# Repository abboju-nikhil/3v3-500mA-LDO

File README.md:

# Single-Cell Li-Ion 3.3V / 500mA Low-Noise Power Supply

> A compact, robust, low-noise **3.3V linear regulator PCB** designed for **single-cell Li-ion batteries**, featuring comprehensive input protection, thermal optimization, and debugging support. Ideal for embedded systems, RF modules, sensors, and precision analog applications. 

---

## 📌 Overview

This project implements a **2-layer PCB** that converts the output of a **single-cell Li-ion battery (3.8V–4.2V)** into a clean, regulated **3.3V** supply capable of delivering up to **500mA** continuous current.

The design emphasizes:

* Low output noise
* High reliability
* Battery efficiency
* Robust input protection
* Thermal performance
* Easy testing and debugging

---

## ✨ Features

* 🔋 Single-cell Li-ion input (3.8V–4.2V)
* ⚡ Fixed 3.3V regulated output
* 🔌 500mA continuous output current
* 🛡 Reverse polarity protection
* ⚠ Resettable overcurrent protection (PTC Fuse)
* ⚡ TVS surge & ESD protection
* 🔥 Thermal pad with via array
* 💡 Power indication LED
* 📈 Dedicated test points
* 🧩 2-layer PCB with optimized power routing

---

## 📊 Specifications

| Parameter             | Value        |
| --------------------- | ------------ |
| Input Voltage         | 3.8V–4.2V DC |
| Output Voltage        | 3.3V DC      |
| Output Current        | 500mA Max    |
| Typical Load          | 450mA        |
| Operating Temperature | 0°C–70°C     |
| PCB Layers            | 2            |
| Board Size            | <40mm × 20mm |

---

# Architecture

```text
Li-Ion Battery
      │
      ▼
Resettable PTC Fuse
      │
      ▼
TVS Diode Protection
      │
      ▼
P-Channel MOSFET
(Reverse Polarity Protection)
      │
      ▼
LP5912-3.3 LDO
      │
      ▼
Output Capacitors
      │
      ▼
3.3V Output Connector
```

---

# Main Components

| Reference | Part           | Purpose                     |
| --------- | -------------- | --------------------------- |
| U1        | LP5912-3.3DRVR | 500mA Low-Noise LDO         |
| Q1        | DMP2035U-7     | Reverse Polarity Protection |
| F1        | MF-NSMF110-2   | Resettable PTC Fuse         |
| D1        | SMAJ5.0CA      | TVS Surge Protection        |
| D2        | BZT52C6V8      | MOSFET Gate Protection      |
| D3        | Green LED      | Power Indicator             |
| C1        | 22µF           | Input Bulk Capacitor        |
| C2        | 100nF          | Input Decoupling            |
| C3        | 10µF           | Output Stability            |
| C4        | 100nF          | High-Frequency Filtering    |

---

# Protection Features

## Reverse Polarity Protection

A **DMP2035U-7 P-Channel MOSFET** replaces the traditional Schottky diode, providing:

* Lower voltage drop
* Higher efficiency
* Better battery utilization
* Automatic reverse battery protection

---

## Overcurrent Protection

The **MF-NSMF110-2 resettable PTC fuse** protects against:

* Output short circuits
* Component failures
* Excessive current draw

The fuse automatically resets once the fault is removed.

---

## Surge & ESD Protection

A **SMAJ5.0CA TVS diode** protects the input from:

* ESD events
* Hot-plug transients
* Voltage spikes
* Input surges

---

## MOSFET Gate Protection

A **6.8V Zener diode (BZT52C6V8)** limits the gate-to-source voltage to protect the MOSFET during transient events.

---

# Capacitor Configuration

## Input Side

| Component | Function                       |
| --------- | ------------------------------ |
| 22µF      | Bulk energy storage            |
| 100nF     | High-frequency noise filtering |

Placed close to the regulator input to minimize parasitic inductance.

---

## Output Side

| Component | Function                       |
| --------- | ------------------------------ |
| 10µF      | Stability & transient response |
| 100nF     | High-frequency filtering       |

Located directly beside the regulator output pin.

---

# Test Points

For simplified debugging and validation:

| Test Point | Signal |
| ---------- | ------ |
| TP1        | VIN    |
| TP2        | VOUT   |
| TP3        | GND    |

Compatible with multimeters and oscilloscopes.

---

# Thermal Design

Worst-case power dissipation:

```text
P = (VIN − VOUT) × IOUT

= (4.2 − 3.3) × 0.5

≈ 0.45 W
```

Thermal improvements include:

* Exposed thermal pad
* Thermal via array
* Continuous ground plane
* Ground stitching vias

These features improve heat dissipation and ensure reliable operation within the specified temperature range.

---

# PCB Layout Highlights

* 2-layer PCB
* Continuous bottom ground plane
* Wide VIN/VOUT copper pours
* Short power paths
* Thermal vias beneath LDO
* Ground stitching
* 45° trace routing
* Clearly labeled silkscreen
* Dedicated debugging test points

---

# Applications

This board is suitable for:

* 🤖 Embedded Systems
* 📡 RF Modules
* 📟 IoT Devices
* 🌡 Sensor Nodes
* 🎧 Low-Noise Analog Circuits
* 🔬 Laboratory Prototypes
* 📷 Portable Electronics

---

# Repository Structure

```text
├── Hardware/
│   ├── Schematic/
│   ├── PCB/
│   ├── Gerbers/
│   └── BOM/
│
├── Images/
│   ├── PCB_3D.png
│   ├── Top_View.png
│   └── Bottom_View.png
│
├── Datasheets/
│
├── Docs/
│   └── Design_Notes.pdf
│
└── README.md
```

---

# Future Improvements

* Buck-Boost version for full battery discharge operation
* Battery charging circuit integration
* Fuel gauge implementation
* USB Type-C power input
* Power-path management
* Load switch enable/disable control

---

# License

This project is released under the **MIT License**.

---

## 👨‍💻 Author

**Nikhil Abboju**
Power Electronics Engineer | PCB Design | Embedded Hardware | KiCad

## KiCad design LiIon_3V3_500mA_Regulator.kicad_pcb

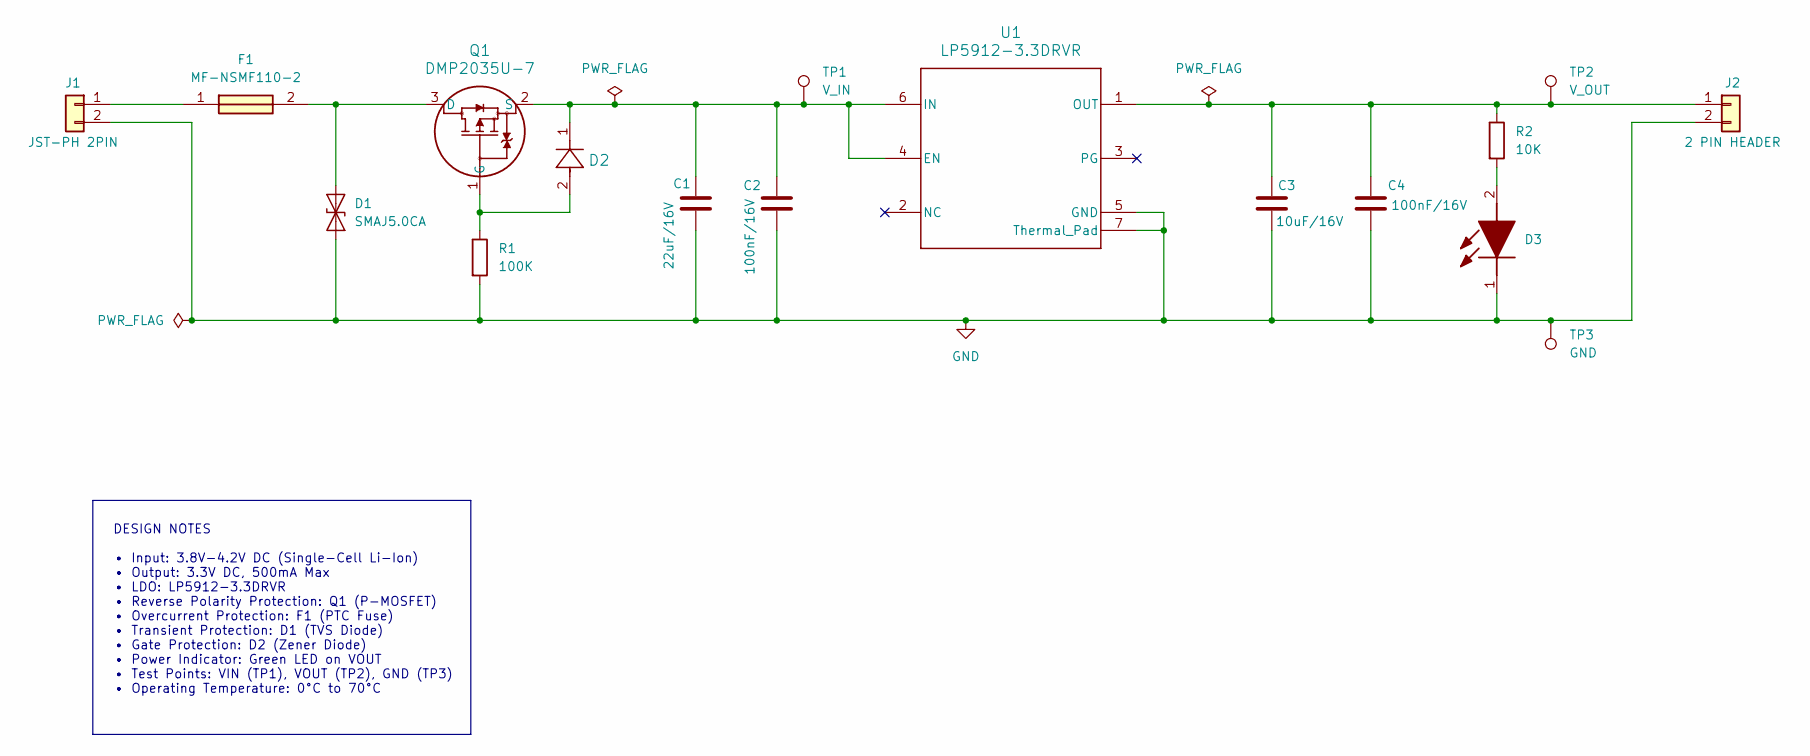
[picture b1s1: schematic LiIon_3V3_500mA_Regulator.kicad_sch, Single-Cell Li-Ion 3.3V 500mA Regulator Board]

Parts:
C1: 22uF/16V; C_0805_2012Metric; MPN CL21A226MOQNNNE
C2, C4: 100nF/16V; C_0603_1608Metric; MPN GCM188R71C104KA37J
C3: 10uF/16V; C_0805_2012Metric; MPN GRM21BZ71C106KE15L
D1: SMAJ5.0CA; D_SMA; MPN SMAJ5.0CA
D2: 6.8V; SOD123_DIO; MPN BZT52C6V8-7-F
D3: LTST-C190KGKT; LEDC1608X80N; MPN LTST-C190KGKT
F1: MF-NSMF110-2; FUSC3216X70N; MPN MF-NSMF110-2
J1: JST-PH 2PIN; B2B-PH-K-S; MPN B2B-PH-K-S
J2: 2 PIN HEADER; 22-23-2021; MPN 22-23-2021
Q1: DMP2035U-7; MPN DMP2035U-7
R1: 100K; R_0603_1608Metric; MPN RC0603FR-07100KL
R2: 10K; R_0603_1608Metric; MPN RC0603FR-0710KL
TP1: V_IN; TestPoint_THTPad_D1.5mm_Drill0.7mm
TP2: V_OUT; TestPoint_THTPad_D1.5mm_Drill0.7mm
TP3: GND; TestPoint_THTPad_D1.5mm_Drill0.7mm
U1: LP5912-3.3DRVR; U1; MPN LP5912-3.3DRVR

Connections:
GND: C1.2, C2.2, C3.2, C4.2, D1.2 (A2), D3.1 (K), J1.2, J2.2, R1.2, TP3.1 (1_1), U1.5 (GND), U1.7 (Thermal_Pad)
unnamed: D1.1 (A1), F1.2, Q1.3 (D)
unnamed: D3.2 (A), R2.2
unnamed: F1.1, J1.1
unnamed: C3.1, C4.1, J2.1, R2.1, TP2.1 (1_1), U1.1 (OUT)
unnamed: D2.2, Q1.1 (G), R1.1
unnamed: C1.1, C2.1, D2.1, Q1.2 (S), TP1.1 (1_1), U1.4 (EN), U1.6 (IN)

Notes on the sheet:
DESIGN NOTES • Input: 3.8V-4.2V DC (Single-Cell Li-Ion) • Output: 3.3V DC, 500mA Max • LDO: LP5912-3.3DRVR • Reverse Polarity Protection: Q1 (P-MOSFET) • Overcurrent Protection: F1 (PTC Fuse) • Transient Protection: D1 (TVS Diode) • Gate Protection: D2 (Zener Diode) • Power Indicator: Green LED on 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

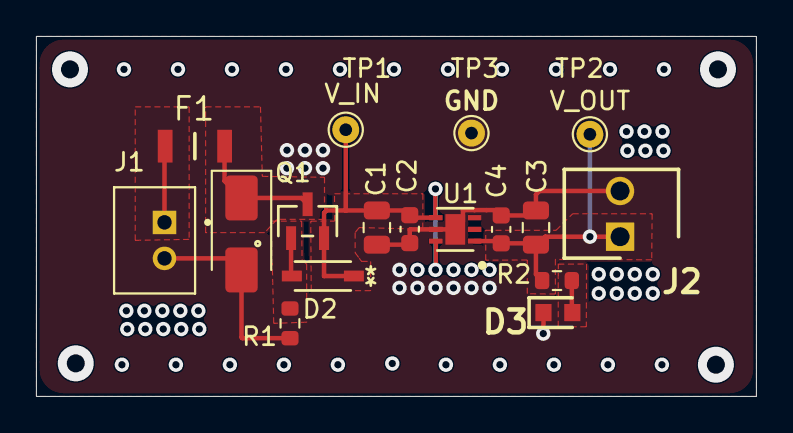
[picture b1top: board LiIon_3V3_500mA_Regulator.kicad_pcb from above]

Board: 2 copper layers, 40.0 x 20.0 mm, 17 parts (0 on the bottom side), 7 nets.

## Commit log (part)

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2026-06-11 added readme
2026-06-28 Add README for Low-Noise Power Supply project
    Added comprehensive documentation for the Single-Cell Li-Ion 3.3V / 500mA Low-Noise Power Supply project, including features, specifications, protection features, thermal design, and future improveme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
